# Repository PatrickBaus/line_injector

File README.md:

# Line Injector
This repository contains the schematics and mechanical files for a line injector.

## Contents
- [Introduction](#introduction)
- [Bode Plot](#bode-plot)
- [PCB Design Files](#pcb-design-files)
- [Mechanical Design Files](#mechanical-design-files)
- [Related Repositories](#related-repositories)
- [Versioning](#versioning)
- [License](#license)

## Introduction
A line injector can be used to inject a ripple voltage into the supply line of a circuit. This can, for example, be used to measure the [power supply rejection ratio (PSRR)](https://en.wikipedia.org/wiki/Power_supply_rejection_ratio) of a regulator.

Key Features:
 * Bandwidth (-3 dB): 6 Hz - 35 MHz (into 50 Ω)
 * Passband transfer function is about 0.95 V/V (@ 5V) and 0.975 V/V (@ 15V)
 * Maximum input voltage: 50 V
 * Maximum current: 5 A
 * Remote sensing inputs to compensate for the voltage drop over the MOSFET

The design was done using [KiCAD 8](https://www.kicad.org/).

## Bode Plot

Additionally, a report from the Bode 100 VNA used to characterize the injector can be found [here](/supplemental/Line%20Injector_JFW.pdf).

Photos of the finished design
------------------------------

### Front

### Back

### PCB

## PCB Design Files
The root folder contains the KiCAD files. The bill of materials can be found on the [releases](../../releases) page along with Gerber files for production.

## Mechanical Design Files
The PCB fits into a Hammond Manufacturing [1457N1201EBK](https://www.hammfg.com/electronics/small-case/extruded/1457-emi) case. Additionally a few drilled holes need to be drilled for the connectors.

## Related Repositories
See the following repositories for more information.

KiCAD footprints: https://github.com/PatrickBaus/footprints.pretty

## Versioning
I use [SemVer](http://semver.org/) for versioning. For the versions available, see the [tags](../../tags) available for this repository.

- MAJOR versions in this context mean a breaking change to the external interface of the hardware like different connectors or functions.
- MINOR versions contain changes to the hardware that only affect the inner workings of the circuit, but otherwise the performance is unaffected.
- PATCH versions do not affect the schematics or invalidate older bill of materials. These changes may include updated components (to replace obsolete parts for example), an updated silkscreen, or fixed typos.

## License
This work is released under the CERN-OHL-W
See [https://ohwr.org/cern_ohl_w_v2.pdf](https://ohwr.org/cern_ohl_w_v2.pdf) or the included LICENSE file for more information.

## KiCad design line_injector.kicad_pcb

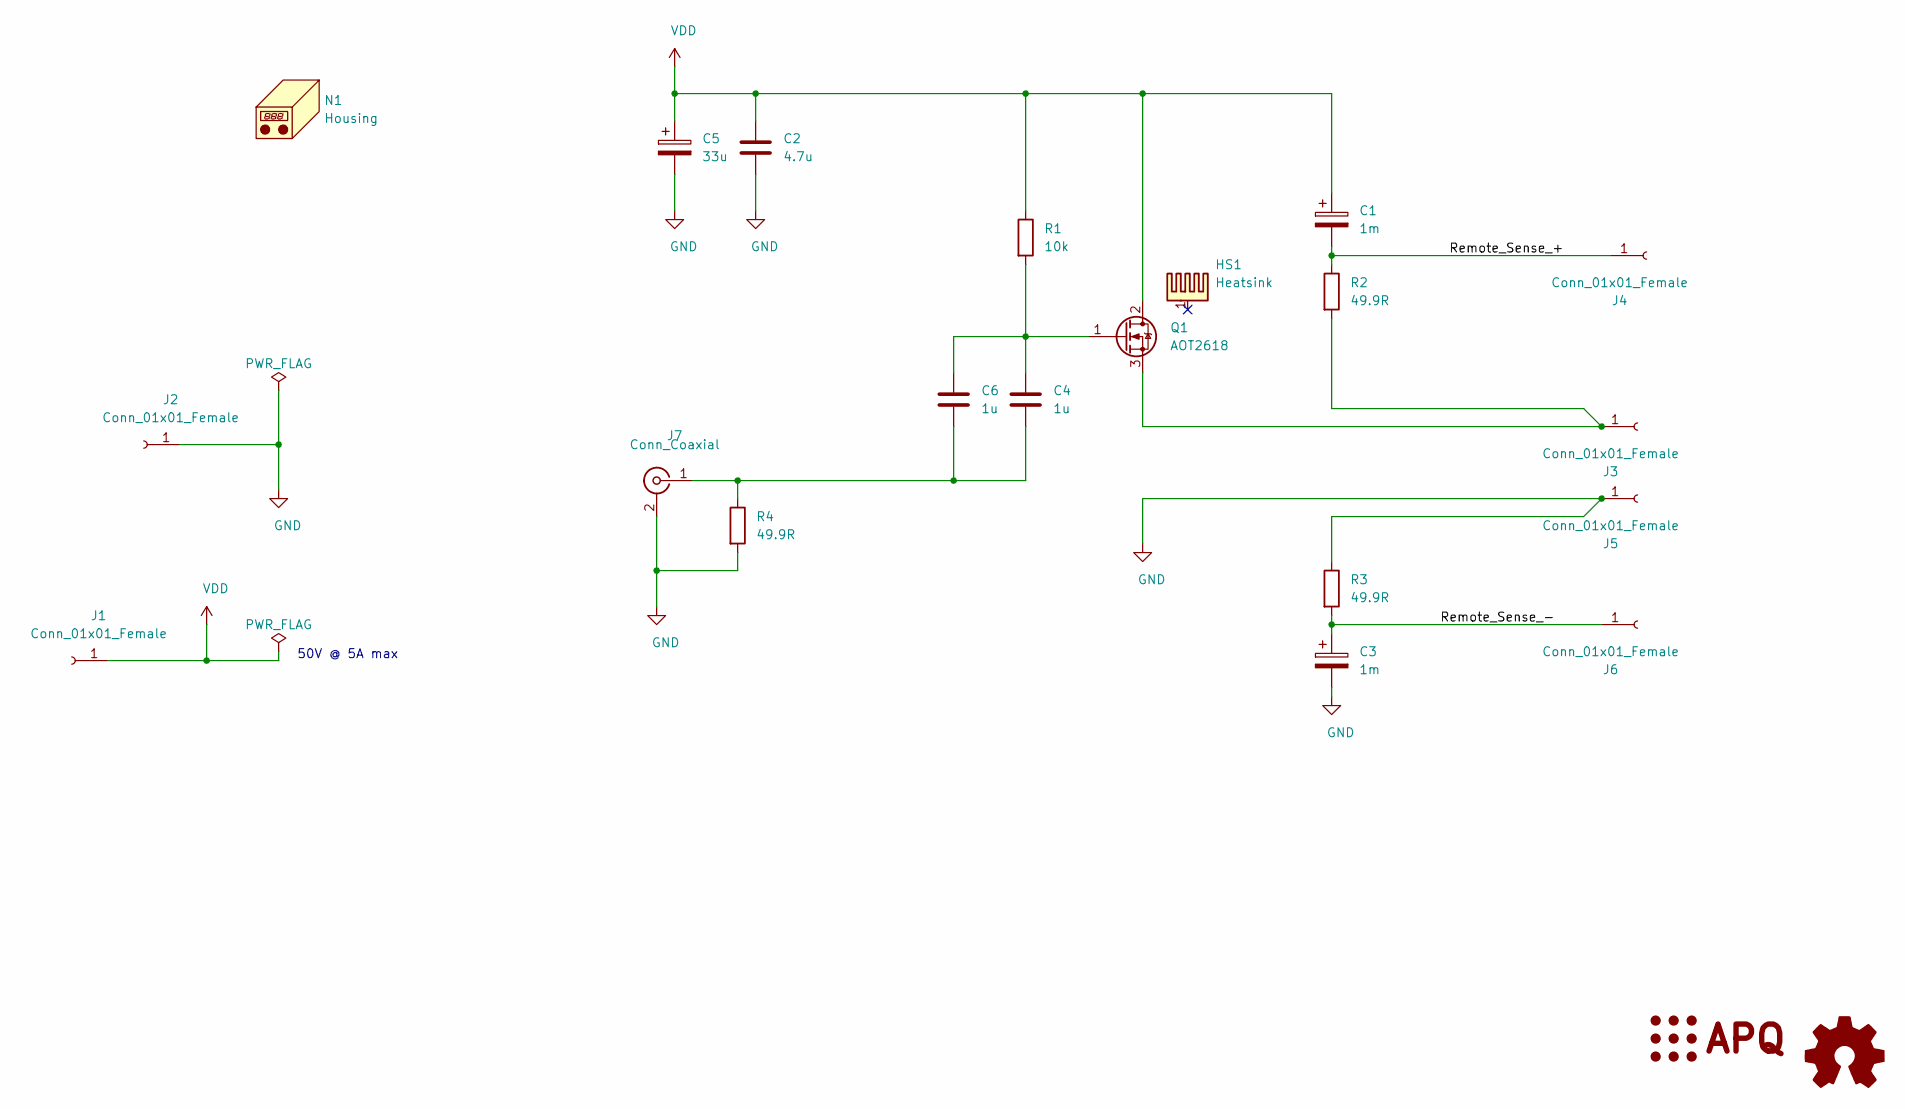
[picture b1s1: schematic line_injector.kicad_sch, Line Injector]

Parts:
C1, C3: 1m; CP_Radial_D18.0mm_P7.50mm
C2: 4.7u; C_1210_3225Metric
C4, C6: 1u; C_1206_3216Metric
C5: 33u; CP_Radial_D10.0mm_P5.00mm
HS1: Heatsink; Heatsink_42x25mm_2xFixation_Ohmite-R-series
J1, J3, J4: Conn_01x01_Female; Banana_Cliff_FCR7350R_S16N-PC_Horizontal
J2, J5, J6: Conn_01x01_Female; Banana_Cliff_FCR7350B_S16N-PC_Horizontal
J7: Conn_Coaxial; BNC_Amphenol_B6252HB-NPP3G-50_Horizontal
LOGO1: Logo_APQ; APQ-Logo_small
LOGO2: Logo_Open_Hardware_Small; OSHW-Logo_7.5x8mm_SilkScreen
N1: Housing
Q1: AOT2618; TO-220-3_Vertical
R1: 10k; R_0805_2012Metric
R2, R3, R4: 49.9R; R_1206_3216Metric

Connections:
/Remote_Sense_+: C1.2, J4.1, R2.1
/Remote_Sense_-: C3.1, J6.1, R3.2
GND: C2.2, C3.2, C5.2, J2.1, J5.1, J7.2 (Ext), R3.1, R4.2
unnamed: J3.1, Q1.3 (S), R2.2
unnamed: C4.2, C6.2, J7.1 (In), R4.1
unnamed: C4.1, C6.1, Q1.1 (G), R1.2
VDD: C1.1, C2.1, C5.1, J1.1, Q1.2 (D), R1.1

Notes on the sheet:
50V @ 5A max

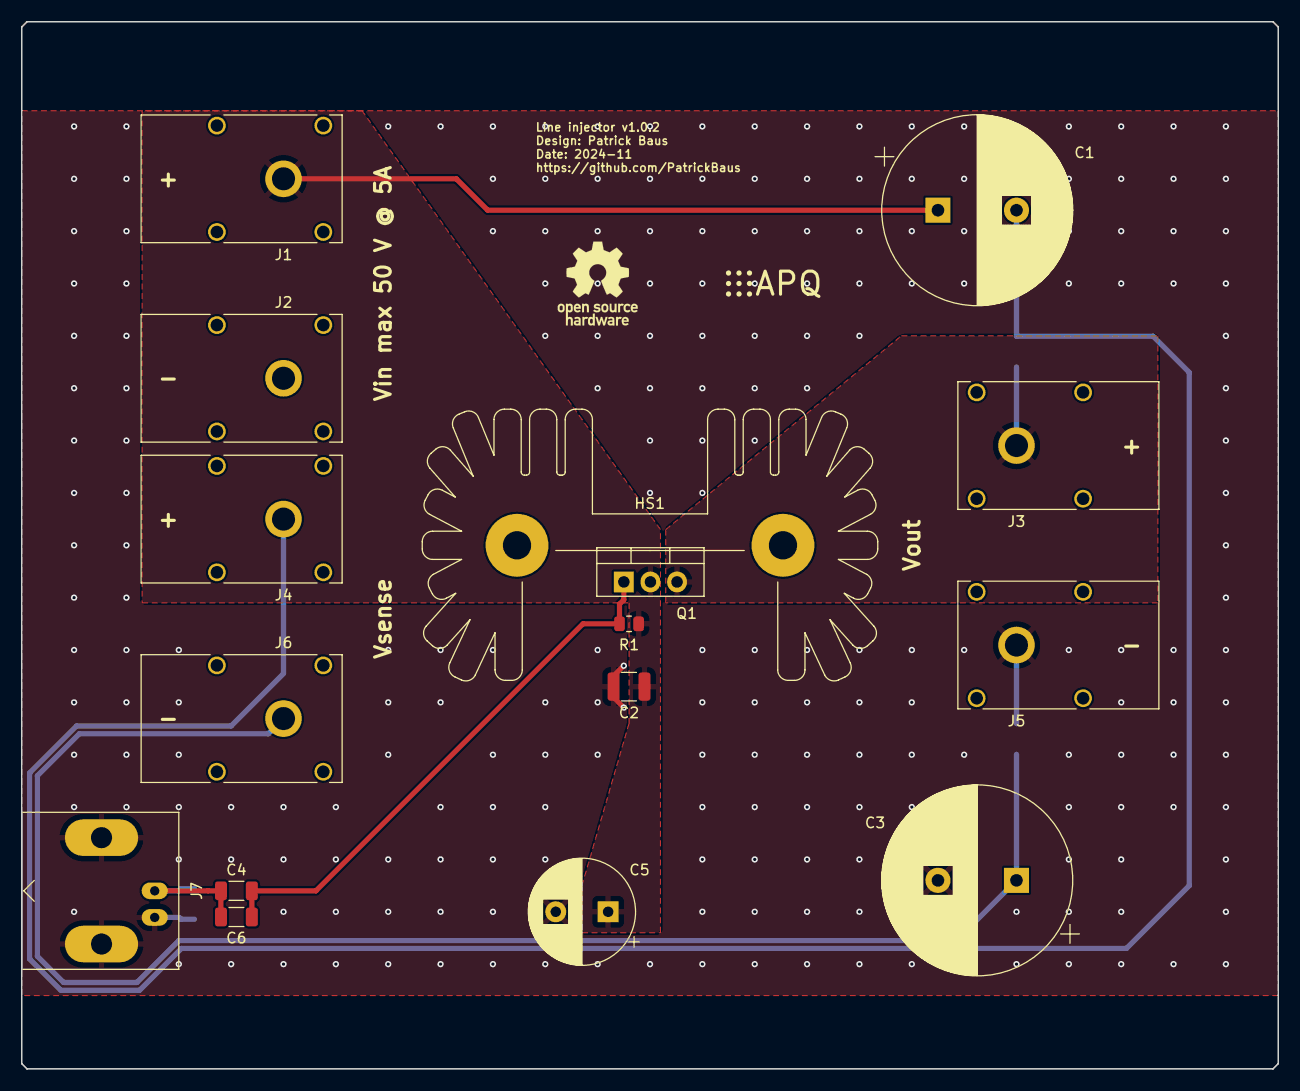
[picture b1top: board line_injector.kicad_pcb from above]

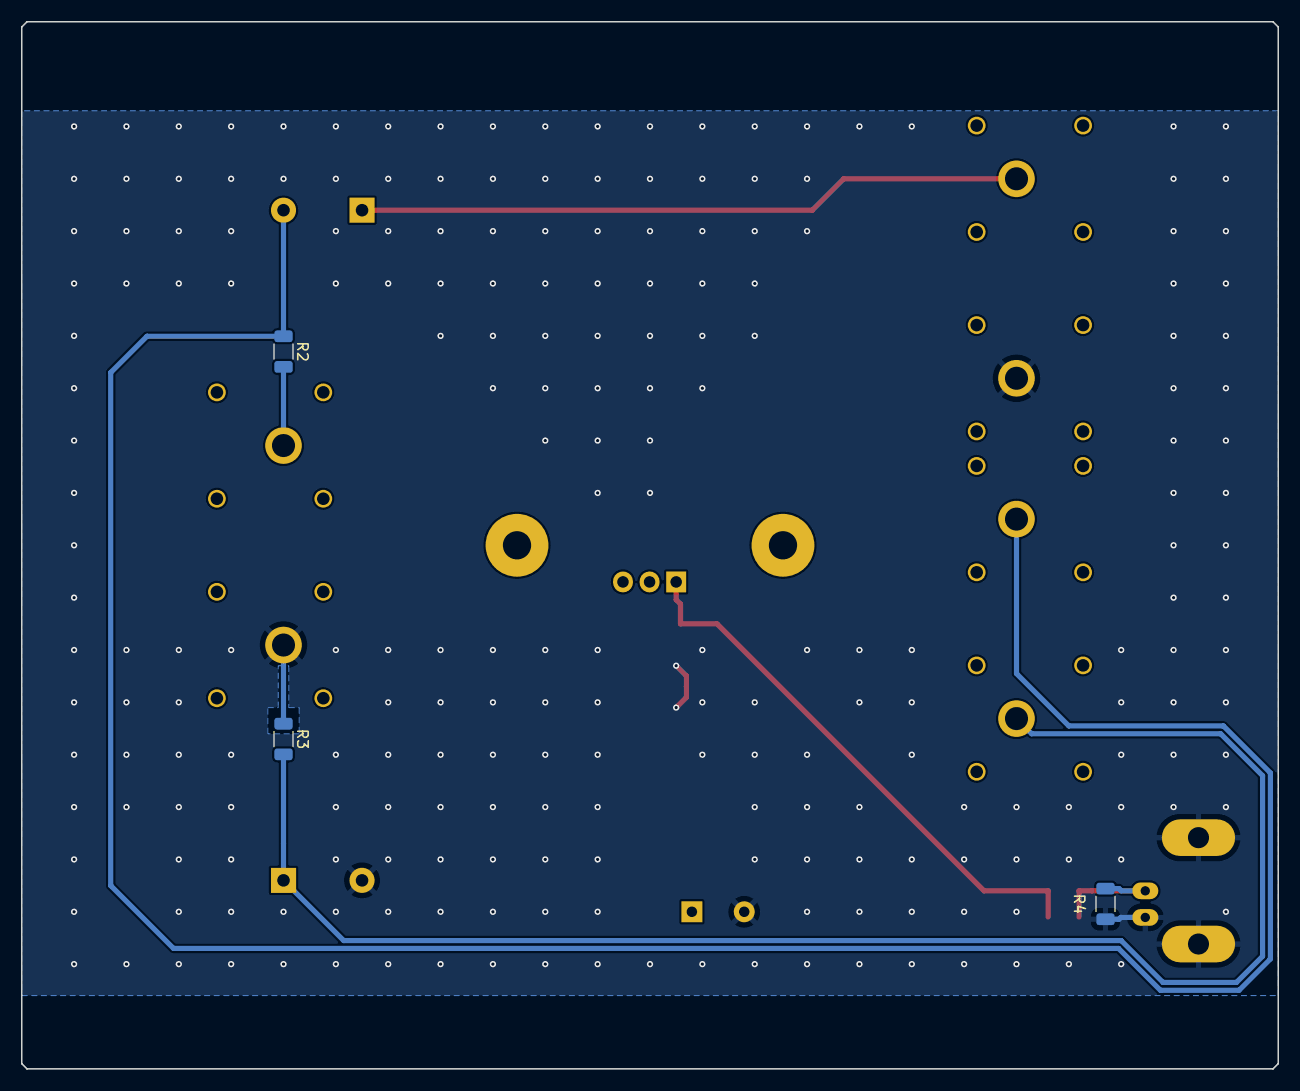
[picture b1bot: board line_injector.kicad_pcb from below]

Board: 2 copper layers, 120.0 x 100.0 mm, 21 parts (3 on the bottom side), 7 nets.

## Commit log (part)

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2022-07-29 Added photos
2022-07-29 Added BOM
2022-07-29 Updated footprints
2023-03-03 Added Bode plot
2023-03-03 Added passband data
2023-03-03 Fixed link to report
2024-11-21 Update to KiCad 8
2024-11-21 Update to KiCad 8 (#1)
2024-11-21 Updated libs
2024-11-21 Updated libs (#2)
2024-11-21 Renamed project files from main.* to line_injector.*
2024-11-21 Renamed project files from main.* to line_injector.* (#3)
2024-11-21 Add CI workflow
2024-11-21 Add DRC excemption for the heatsink
2024-11-21 Remove BOM from git
2024-11-21 Add CI workflow (#4)
    * Add CI workflow
    * Remove BOM from git
2024-11-21 Udpated license to CERN-OHL-W
2024-11-21 Udpated license to CERN-OHL-W (#5)
2024-11-21 Udpated readme with the standard design
2024-11-21 Udpated readme with the standard design (#6)
2024-11-21 Bump version to 1.0.2
2024-11-21 Removed unused links
2024-11-21 Added RoHS info
    Added temperature data
2024-11-21 Added RoHS info (#7)
    Added temperature data
2024-11-21 Fixed typo
2025-11-26 Bump libraries from `80d58ef` to `ba5563d`
    Bumps [libraries](https://github.com/PatrickBaus/KiCad-libraries) from `80d58ef` to `ba5563d`.
    - [Commits](https://github.com/PatrickBaus/KiCad-libraries/compare/80d58efa29fc28aa49b090516bd5b7168ac740c8...ba5563d66c23dea06d561adcb039ddac5a03efdf)
    ---
    updated-dependencies:
    - dependency-name: libraries
    dependency-version: ba5563d66c23dea06d561adcb039ddac5a03efdf
2025-11-26 Bump libraries from `80d58ef` to `ba5563d` (#8)
    Bumps [libraries](https://github.com/PatrickBaus/KiCad-libraries) from `80d58ef` to `ba5563d`.
    - [Commits](https://github.com/PatrickBaus/KiCad-libraries/compare/80d58efa29fc28aa49b090516bd5b7168ac740c8...ba5563d66c23dea06d561adcb039ddac5a03efdf)
    ---
    updated-dependencies:
    - dependency-name: libraries
    dependency-version: ba5563d66c23dea06d561adcb039ddac5a03efdf
2025-12-17 Bump libraries from `ba5563d` to `d79317d`
    Bumps [libraries](https://github.com/PatrickBaus/KiCad-libraries) from `ba5563d` to `d79317d`.
    - [Commits](https://github.com/PatrickBaus/KiCad-libraries/compare/ba5563d66c23dea06d561adcb039ddac5a03efdf...d79317d926704a58090a36fac06bfafa731a048b)
    ---
    updated-dependencies:
    - dependency-name: libraries
    dependency-version: d79317d926704a58090a36fac06bfafa731a048b
2025-12-17 Bump libraries from `ba5563d` to `d79317d` (#9)
    Bumps [libraries](https://github.com/PatrickBaus/KiCad-libraries) from `ba5563d` to `d79317d`.
    - [Commits](https://github.com/PatrickBaus/KiCad-libraries/compare/ba5563d66c23dea06d561adcb039ddac5a03efdf...d79317d926704a58090a36fac06bfafa731a048b)
    ---
    updated-dependencies:
    - dependency-name: libraries
    dependency-version: d79317d926704a58090a36fac06bfafa731a048b
2026-02-09 Bump libraries from `d79317d` to `4179135`
    Bumps [libraries](https://github.com/PatrickBaus/KiCad-libraries) from `d79317d` to `4179135`.
    - [Commits](https://github.com/PatrickBaus/KiCad-libraries/compare/d79317d926704a58090a36fac06bfafa731a048b...41791358010d2de5d2401e25bd30de257630acf6)
    ---
    updated-dependencies:
    - dependency-name: libraries
    dependency-version: 41791358010d2de5d2401e25bd30de257630acf6
2026-02-09 Bump libraries from `d79317d` to `4179135` (#10)
    Bumps [libraries](https://github.com/PatrickBaus/KiCad-libraries) from `d79317d` to `4179135`.
    - [Commits](https://github.com/PatrickBaus/KiCad-libraries/compare/d79317d926704a58090a36fac06bfafa731a048b...41791358010d2de5d2401e25bd30de257630acf6)
    ---
    updated-dependencies:
    - dependency-name: libraries
    dependency-version: 41791358010d2de5d2401e25bd30de257630acf6
2026-04-30 [gha] Bump actions/upload-artifact from 4 to 7
    Bumps [actions/upload-artifact](https://github.com/actions/upload-artifact) from 4 to 7.
    - [Release notes](https://github.com/actions/upload-artifact/releases)
    - [Commits](https://github.com/actions/upload-artifact/compare/v4...v7)
    ---
    updated-dependencies:
    - dependency-name: actions/upload-artifact
2026-04-30 [gha] Bump actions/download-artifact from 4 to 8
    Bumps [actions/download-artifact](https://github.com/actions/download-artifact) from 4 to 8.
    - [Release notes](https://github.com/actions/download-artifact/releases)
    - [Commits](https://github.com/actions/download-artifact/compare/v4...v8)
    ---
    updated-dependencies:
    - dependency-name: actions/download-artifact
2026-04-30 [gha] Bump actions/checkout from 4 to 6
    Bumps [actions/checkout](https://github.com/actions/checkout) from 4 to 6.
    - [Release notes](https://github.com/actions/checkout/releases)
    - [Changelog](https://github.com/actions/checkout/blob/main/CHANGELOG.md)
    - [Commits](https://github.com/actions/checkout/compare/v4...v6)
    ---
    updated-dependencies:
2026-04-30 [gha] Bump actions/upload-artifact from 4 to 7 (#11)
    Bumps [actions/upload-artifact](https://github.com/actions/upload-artifact) from 4 to 7.
    - [Release notes](https://github.com/actions/upload-artifact/releases)
    - [Commits](https://github.com/actions/upload-artifact/compare/v4...v7)
    ---
    updated-dependencies:
    - dependency-name: actions/upload-artifact
2026-04-30 [gha] Bump actions/checkout from 4 to 6 (#13)
    Bumps [actions/checkout](https://github.com/actions/checkout) from 4 to 6.
    - [Release notes](https://github.com/actions/checkout/releases)
    - [Changelog](https://github.com/actions/checkout/blob/main/CHANGELOG.md)
    - [Commits](https://github.com/actions/checkout/compare/v4...v6)
    ---
    updated-dependencies:
2026-04-30 [gha] Bump actions/download-artifact from 4 to 8 (#12)
    Bumps [actions/download-artifact](https://github.com/actions/download-artifact) from 4 to 8.
    - [Release notes](https://github.com/actions/download-artifact/releases)
    - [Commits](https://github.com/actions/download-artifact/compare/v4...v8)
    ---
    updated-dependencies:
    - dependency-name: actions/download-artifact
2026-06-19 [gha] Bump actions/checkout from 6 to 7
    Bumps [actions/checkout](https://github.com/actions/checkout) from 6 to 7.
    - [Release notes](https://github.com/actions/checkout/releases)
    - [Changelog](https://github.com/actions/checkout/blob/main/CHANGELOG.md)
    - [Commits](https://github.com/actions/checkout/compare/v6...v7)
    ---
    updated-dependencies:
2026-06-19 [gha] Bump actions/checkout from 6 to 7 (#14)
    Bumps [actions/checkout](https://github.com/actions/checkout) from 6 to 7.
    - [Release notes](https://github.com/actions/checkout/releases)
    - [Changelog](https://github.com/actions/checkout/blob/main/CHANGELOG.md)
    - [Commits](https://github.com/actions/checkout/compare/v6...v7)
    ---
    updated-dependencies:

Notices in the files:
line_injector.kicad_pcb:
Copyright (©) 2024, Patrick Baus
Licensed under CERN OHL-W v2.0
